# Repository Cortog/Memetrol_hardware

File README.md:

## Context
This repository contains the hardware design files for the Memetrol project. This project can control three washing machines and one dryer. Users can authenticate themselves using an RFID badge. The system logs the usage of the machines. A webserver on the system serves these logs to the administrator.

## Hardware
The hardware consists of a Raspberry Pi zero W and a Waveshare RP2040-zero both mounted on the base PCB. This PCB also contains the power supply, the relay drivers and analog circuitry for the current sensors. The Raspberry Pi is connected to the Waveshare RP2040-zero with UART. The Waveshare RP2040-zero is connected to the relay drivers and the current measurement circuitry. The Raspberry Pi is connected to the rest of the peripherals using a 20 pin ribbon cable. This cable goes to the door PCB, at which point the connections to the buttons, the LCD and the RFID reader are broken out.

## Changes for the next revision
- Not enough mounting holes were placed on the main PCB. In the end I drilled out the 2.5 mm mounting holes for the Raspberry Pi to 3 mm and drilled an extra one here: [image](extra_hole_location.png). In a future revision the mounting holes should be placed in the correct locations.
- R25 was not needed. This is the resistor in series with the buzzer. The volume can be controlled by varying the duty cycle of the PWM signal. This resistor should be removed in the next revision.
- The buzzer is not loud enough, a different buzzer should be used.
- The connectors for the relays should be changed, currently it consists of two connectors, one for + and one for ground. It should be changed to four connectors, one for each relay, this makes the connections more clear. The current labeling on the PCB is also not correct, where it says Ground it should be 12 volt.
- The analog circuitry for the current measurement could have its own 3.3 volt, or even a 1.65 volt regulator, this might make the measurements more stable.
- The rp2040-zero should know if the override switches are pressed, this would make calibration easier, since the rp2040-zero can then know if it should be measuring zero current or not.
- The electrolytic capacitors in the analog circuitry could be a lot smaller, these were only used because I had them laying around.
- An input power capacitory should be added.
- Maybe an aditional button should be added to the main PCB, this could be used for resetting passwords.
- In the current design a solderbridge is used to select between 5 volts and 12 volts for the button led power, with 12 volts being the default. However, the button leds can only handle up to 6 volts. The door PCB should be changed so that the leds can only be powered from the 5 volt rail.
- During the building of the PCB several mosfets broke, the gate was at around one volt even though it was being pulled down. After replacing them it was improved, but I also added a 10k resistor in parallel with the button leds which improved the leds realy turning off when the gate was being pulled down. This situation should be investigated further.
- Maybe an RFID interupt pin can be added to the door PCB, this would make the system more responsive and use less cpu time.
- The RFID and the LCD are on the same LCD bus, but this makes the RFID reader misbehave. Therefore it needs to be reset every time it is used. This should be fixed in the next revision.

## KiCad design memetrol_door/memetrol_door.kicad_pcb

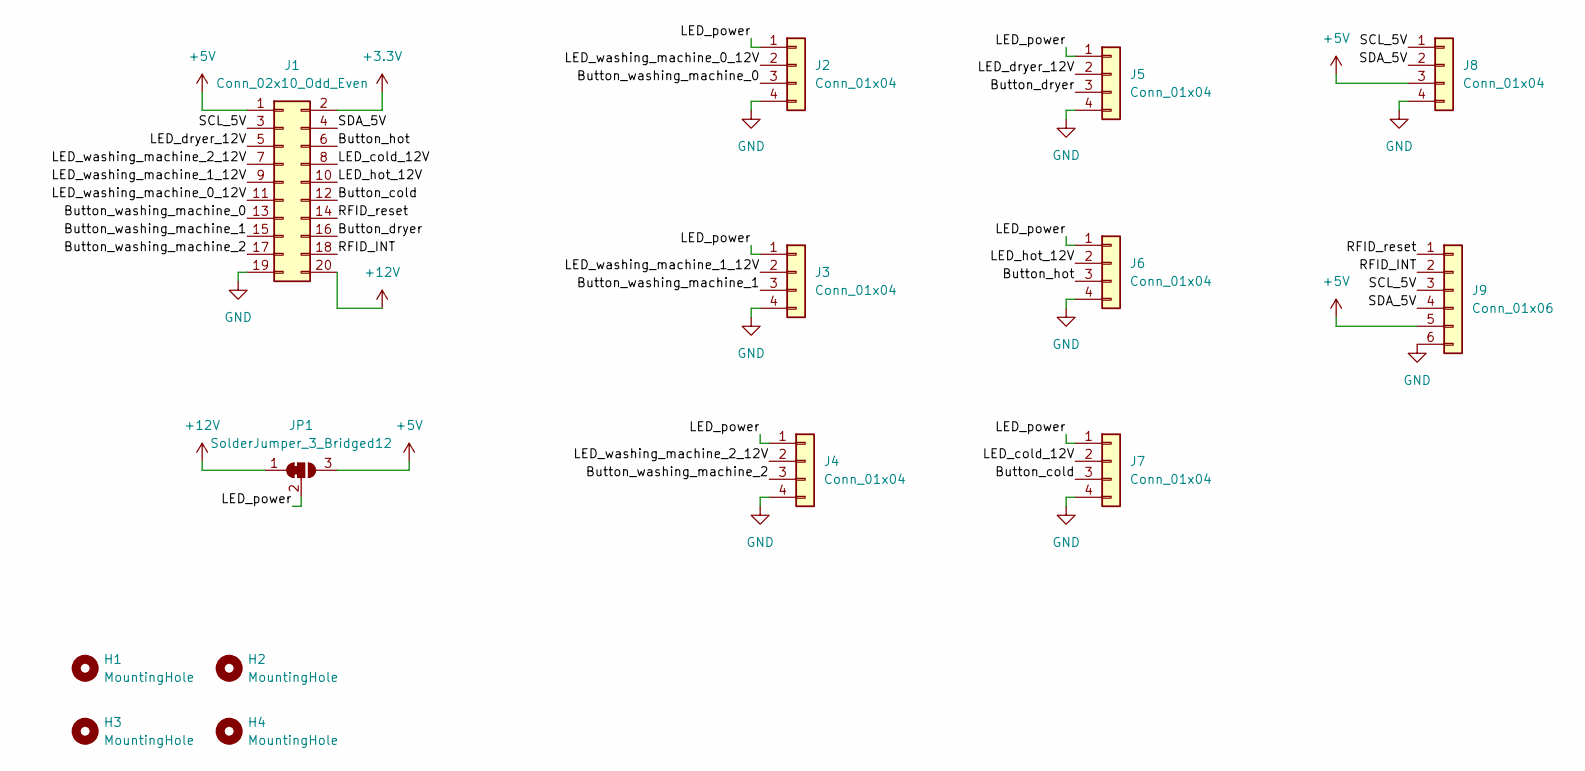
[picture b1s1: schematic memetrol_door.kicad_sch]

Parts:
H1, H2, H3, H4: MountingHole; MountingHole_3.2mm_M3
J1: Conn_02x10_Odd_Even; IDC-Header_2x10_P2.54mm_Vertical
J2, J3, J4, J5, J6, J7, J8: Conn_01x04; JST_PH_B4B-PH-K_1x04_P2.00mm_Vertical
J9: Conn_01x06; JST_PH_B6B-PH-K_1x06_P2.00mm_Vertical
JP1: SolderJumper_3_Bridged12; SolderJumper-3_P1.3mm_Bridged12_Pad1.0x1.5mm

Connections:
+3.3V: J1.2
+5V: J1.1, J8.3, J9.5, JP1.3 (B)
+12V: J1.20, JP1.1 (A)
/Button_cold: J1.12, J7.3
/Button_dryer: J1.16, J5.3
/Button_hot: J1.6, J6.3
/Button_washing_machine_0: J1.13, J2.3
/Button_washing_machine_1: J1.15, J3.3
/Button_washing_machine_2: J1.17, J4.3
/LED_cold_12V: J1.8, J7.2
/LED_dryer_12V: J1.5, J5.2
/LED_hot_12V: J1.10, J6.2
/LED_power: J2.1, J3.1, J4.1, J5.1, J6.1, J7.1, JP1.2 (C)
/LED_washing_machine_0_12V: J1.11, J2.2
/LED_washing_machine_1_12V: J1.9, J3.2
/LED_washing_machine_2_12V: J1.7, J4.2
/RFID_INT: J1.18, J9.2
/RFID_reset: J1.14, J9.1
/SCL_5V: J1.3, J8.1, J9.3
/SDA_5V: J1.4, J8.2, J9.4
GND: J1.19, J2.4, J3.4, J4.4, J5.4, J6.4, J7.4, J8.4, J9.6

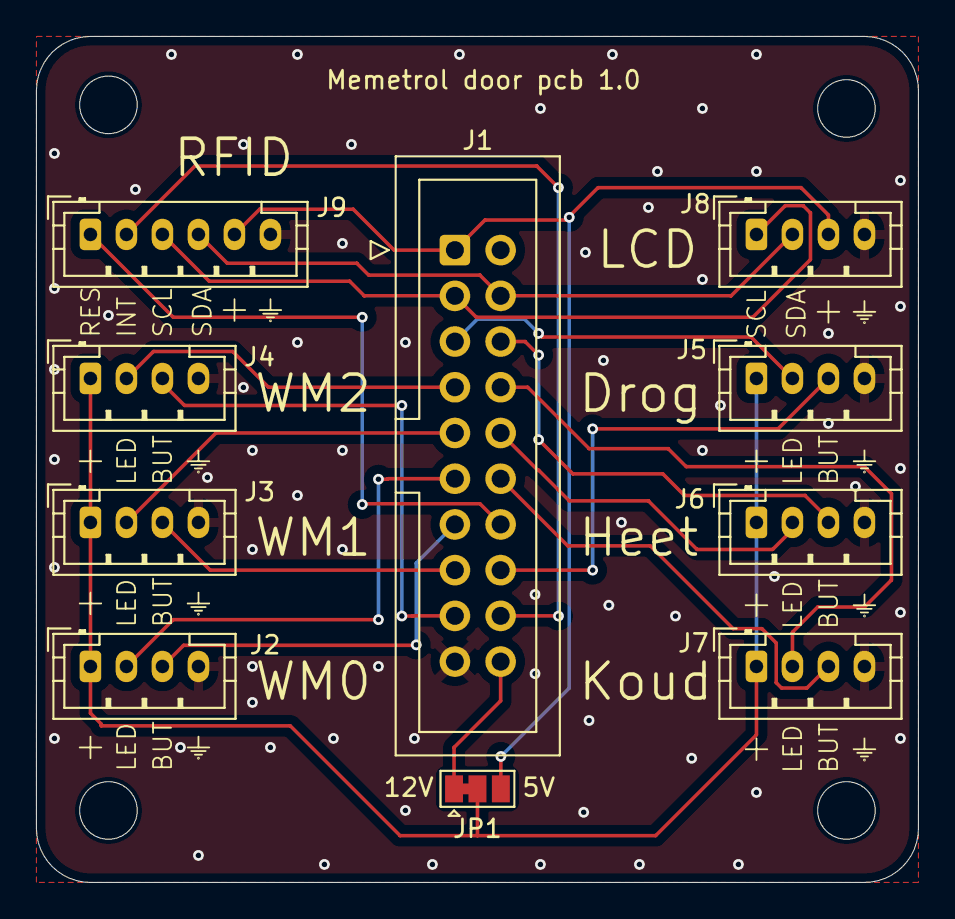
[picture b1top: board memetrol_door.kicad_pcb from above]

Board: 2 copper layers, 49.0 x 47.0 mm, 14 parts (0 on the bottom side), 20 nets.

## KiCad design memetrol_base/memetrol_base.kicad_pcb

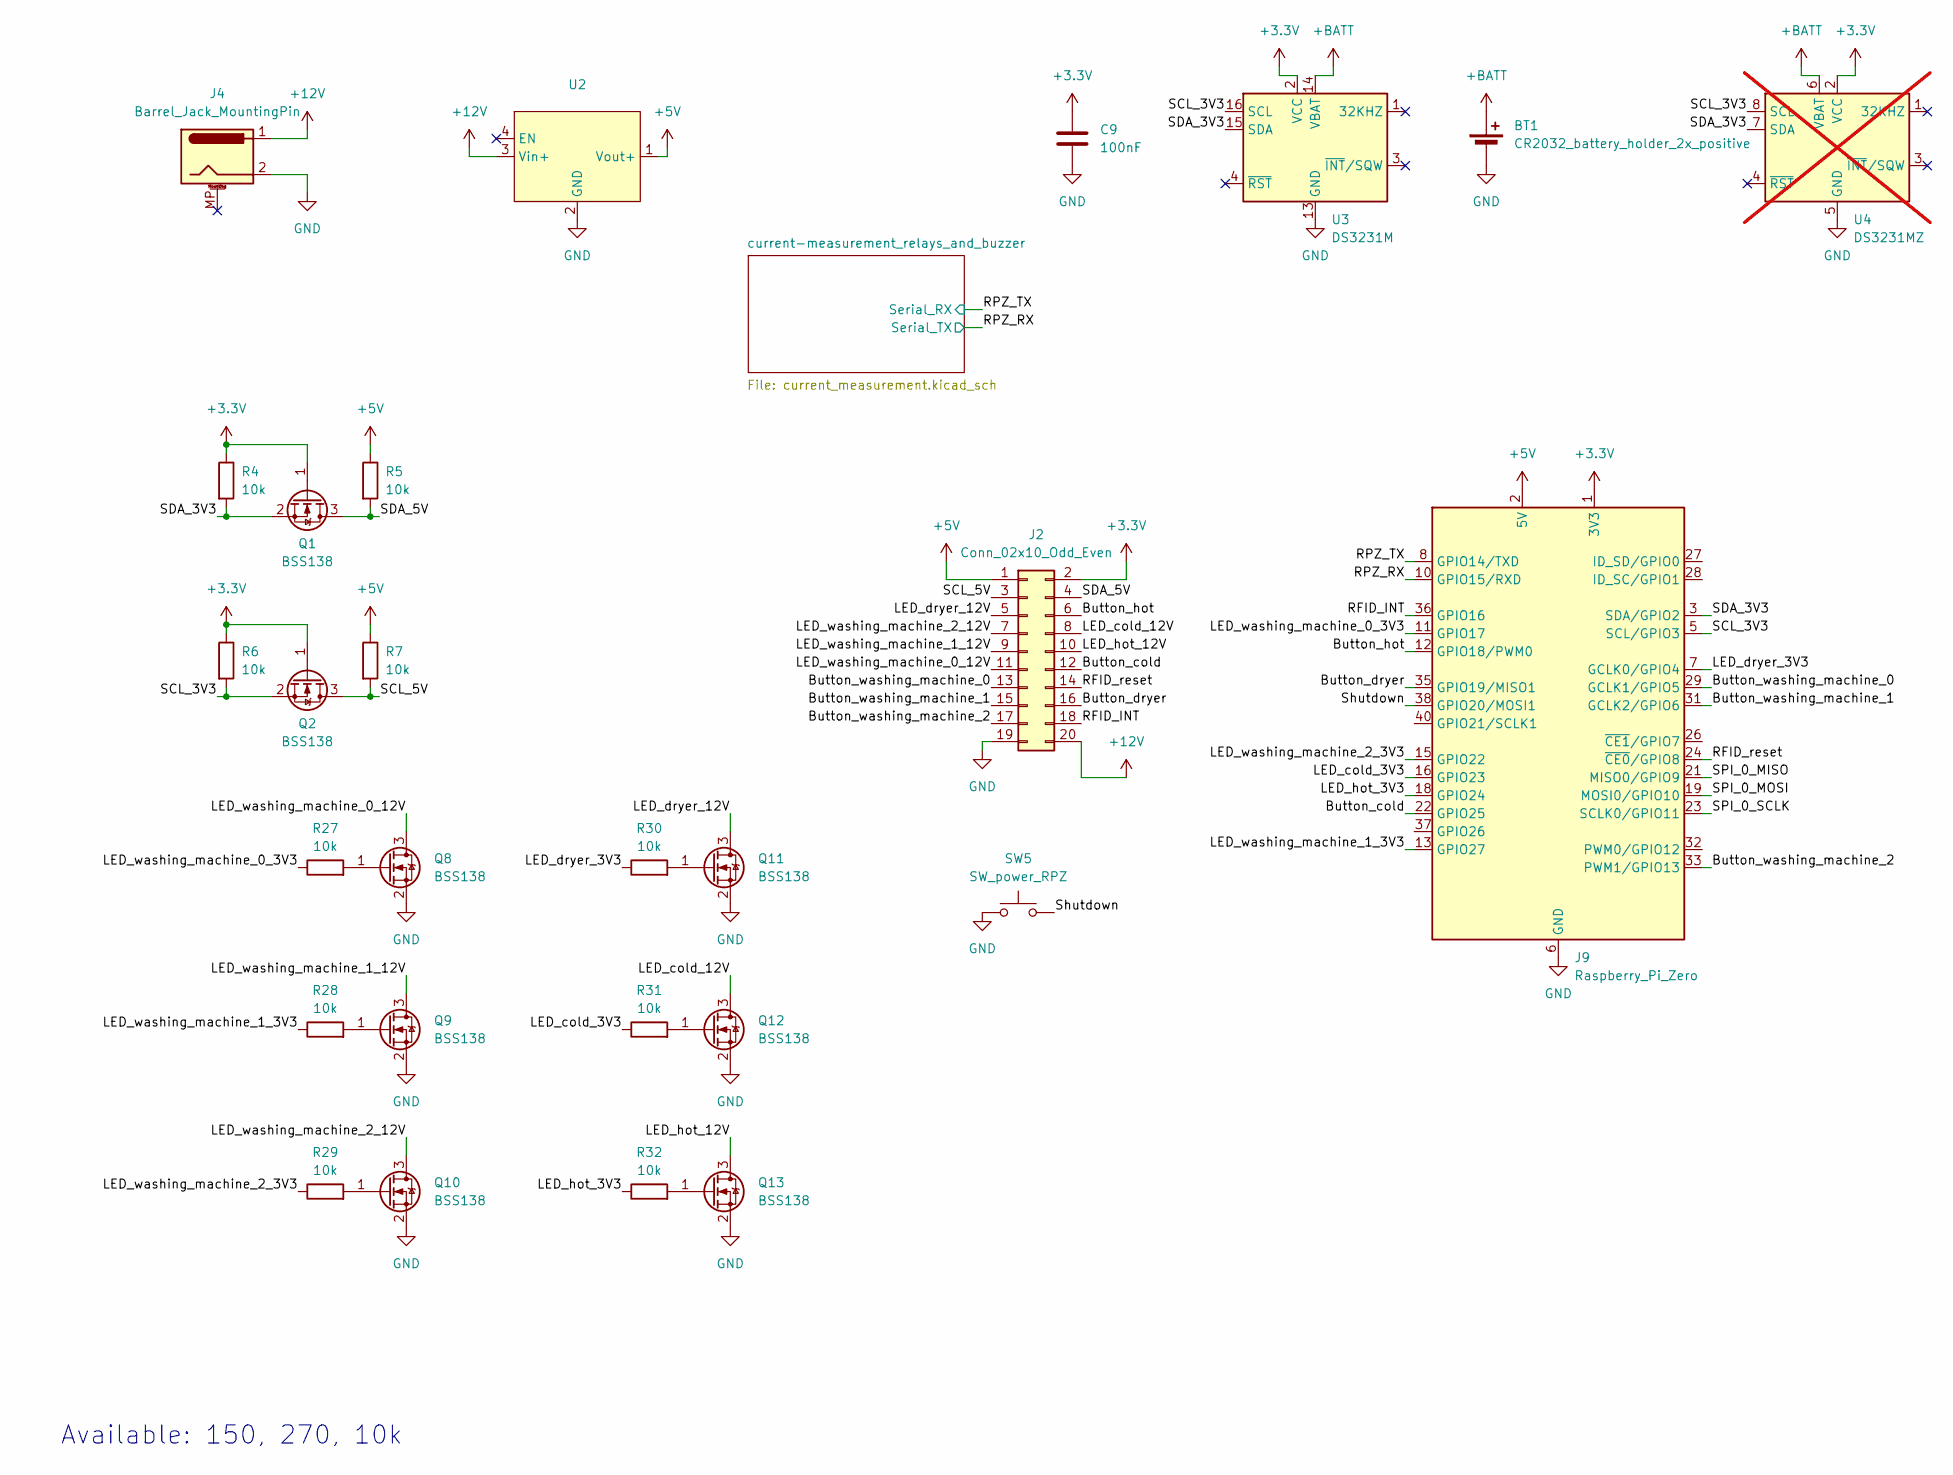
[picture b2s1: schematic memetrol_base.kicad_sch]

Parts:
BT1: CR2032_battery_holder_2x_positive; RS_PRO_CR2032_237-8358
C9: 100nF; C_0805_2012Metric_Pad1.18x1.45mm_HandSolder
J2: Conn_02x10_Odd_Even; IDC-Header_2x10_P2.54mm_Vertical
J4: Barrel_Jack_MountingPin; BarrelJack_Horizontal
J9: Raspberry_Pi_Zero; Raspberry_Pi_Zero_Socketed_THT_FaceUp_MountingHoles
Q1, Q2, Q8, Q9, Q10, Q11, Q12, Q13: BSS138; SOT-323_SC-70_Handsoldering
R4, R5, R6, R7, R27, R28, R29, R30, R31, R32: 10k; R_0805_2012Metric_Pad1.20x1.40mm_HandSolder
SW5: SW_power_RPZ; SW_PUSH_6mm_H7.3mm
U2: MP2315_board_vertical
U3: DS3231M; SOIC-16W_7.5x10.3mm_P1.27mm
U4: DS3231MZ; SOIC-8_3.9x4.9mm_P1.27mm; not fitted

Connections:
+3.3V: C9.1, J2.2, J9.1 (3V3), J9.17 (3V3), Q1.1 (G), Q2.1 (G), R4.1, R6.1, U3.2 (VCC), U4.2 (VCC)
+5V: J2.1, J9.2 (5V), J9.4 (5V), R5.1, R7.1, U2.1 (Vout+); also elsewhere on the board
+12V: J2.20, J4.1, U2.3 (Vin+); also elsewhere on the board
+BATT: BT1.1 (+), BT1.2 (+), U3.14 (VBAT), U4.6 (VBAT)
/Button_cold: J2.12, J9.22 (GPIO25)
/Button_dryer: J2.16, J9.35 (GPIO19/MISO1)
/Button_hot: J2.6, J9.12 (GPIO18/PWM0)
/Button_washing_machine_0: J2.13, J9.29 (GCLK1/GPIO5)
/Button_washing_machine_1: J2.15, J9.31 (GCLK2/GPIO6)
/Button_washing_machine_2: J2.17, J9.33 (PWM1/GPIO13)
/LED_cold_3V3: J9.16 (GPIO23), R31.1
/LED_cold_12V: J2.8, Q12.3 (D)
/LED_dryer_3V3: J9.7 (GCLK0/GPIO4), R30.1
/LED_dryer_12V: J2.5, Q11.3 (D)
/LED_hot_3V3: J9.18 (GPIO24), R32.1
/LED_hot_12V: J2.10, Q13.3 (D)
/LED_washing_machine_0_3V3: J9.11 (GPIO17), R27.1
/LED_washing_machine_0_12V: J2.11, Q8.3 (D)
/LED_washing_machine_1_3V3: J9.13 (GPIO27), R28.1
/LED_washing_machine_1_12V: J2.9, Q9.3 (D)
/LED_washing_machine_2_3V3: J9.15 (GPIO22), R29.1
/LED_washing_machine_2_12V: J2.7, Q10.3 (D)
/RFID_INT: J2.18, J9.36 (GPIO16)
/RFID_reset: J2.14, J9.24 (~CE0/GPIO8)
/RPZ_RX: J9.10 (GPIO15/RXD); also elsewhere on the board
/RPZ_TX: J9.8 (GPIO14/TXD); also elsewhere on the board
/SCL_3V3: J9.5 (SCL/GPIO3), Q2.2 (S), R6.2, U3.16 (SCL), U4.8 (SCL)
/SCL_5V: J2.3, Q2.3 (D), R7.2
/SDA_3V3: J9.3 (SDA/GPIO2), Q1.2 (S), R4.2, U3.15 (SDA), U4.7 (SDA)
/SDA_5V: J2.4, Q1.3 (D), R5.2
/SPI_0_MISO: J9.21 (MISO0/GPIO9)
/SPI_0_MOSI: J9.19 (MOSI0/GPIO10)
/SPI_0_SCLK: J9.23 (SCLK0/GPIO11)
/Shutdown: J9.38 (GPIO20/MOSI1), SW5.2
GND: BT1.3 (-), C9.2, J2.19, J4.2, J9.6 (GND), J9.9 (GND), J9.14 (GND), J9.20 (GND), J9.25 (GND), J9.30 (GND), J9.34 (GND), J9.39 (GND), Q8.2 (S), Q9.2 (S), Q10.2 (S), Q11.2 (S), Q12.2 (S), Q13.2 (S), SW5.1, U2.2 (GND), U3.5 (GND), U3.6 (GND), U3.7 (GND), U3.8 (GND), U3.9 (GND), U3.10 (GND), U3.11 (GND), U3.12 (GND), U3.13 (GND), U4.5 (GND); also elsewhere on the board
unnamed: Q8.1 (G), R27.2
unnamed: Q9.1 (G), R28.2
unnamed: Q10.1 (G), R29.2
unnamed: Q11.1 (G), R30.2
unnamed: Q12.1 (G), R31.2
unnamed: Q13.1 (G), R32.2

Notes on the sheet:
Available: 150, 270, 10k

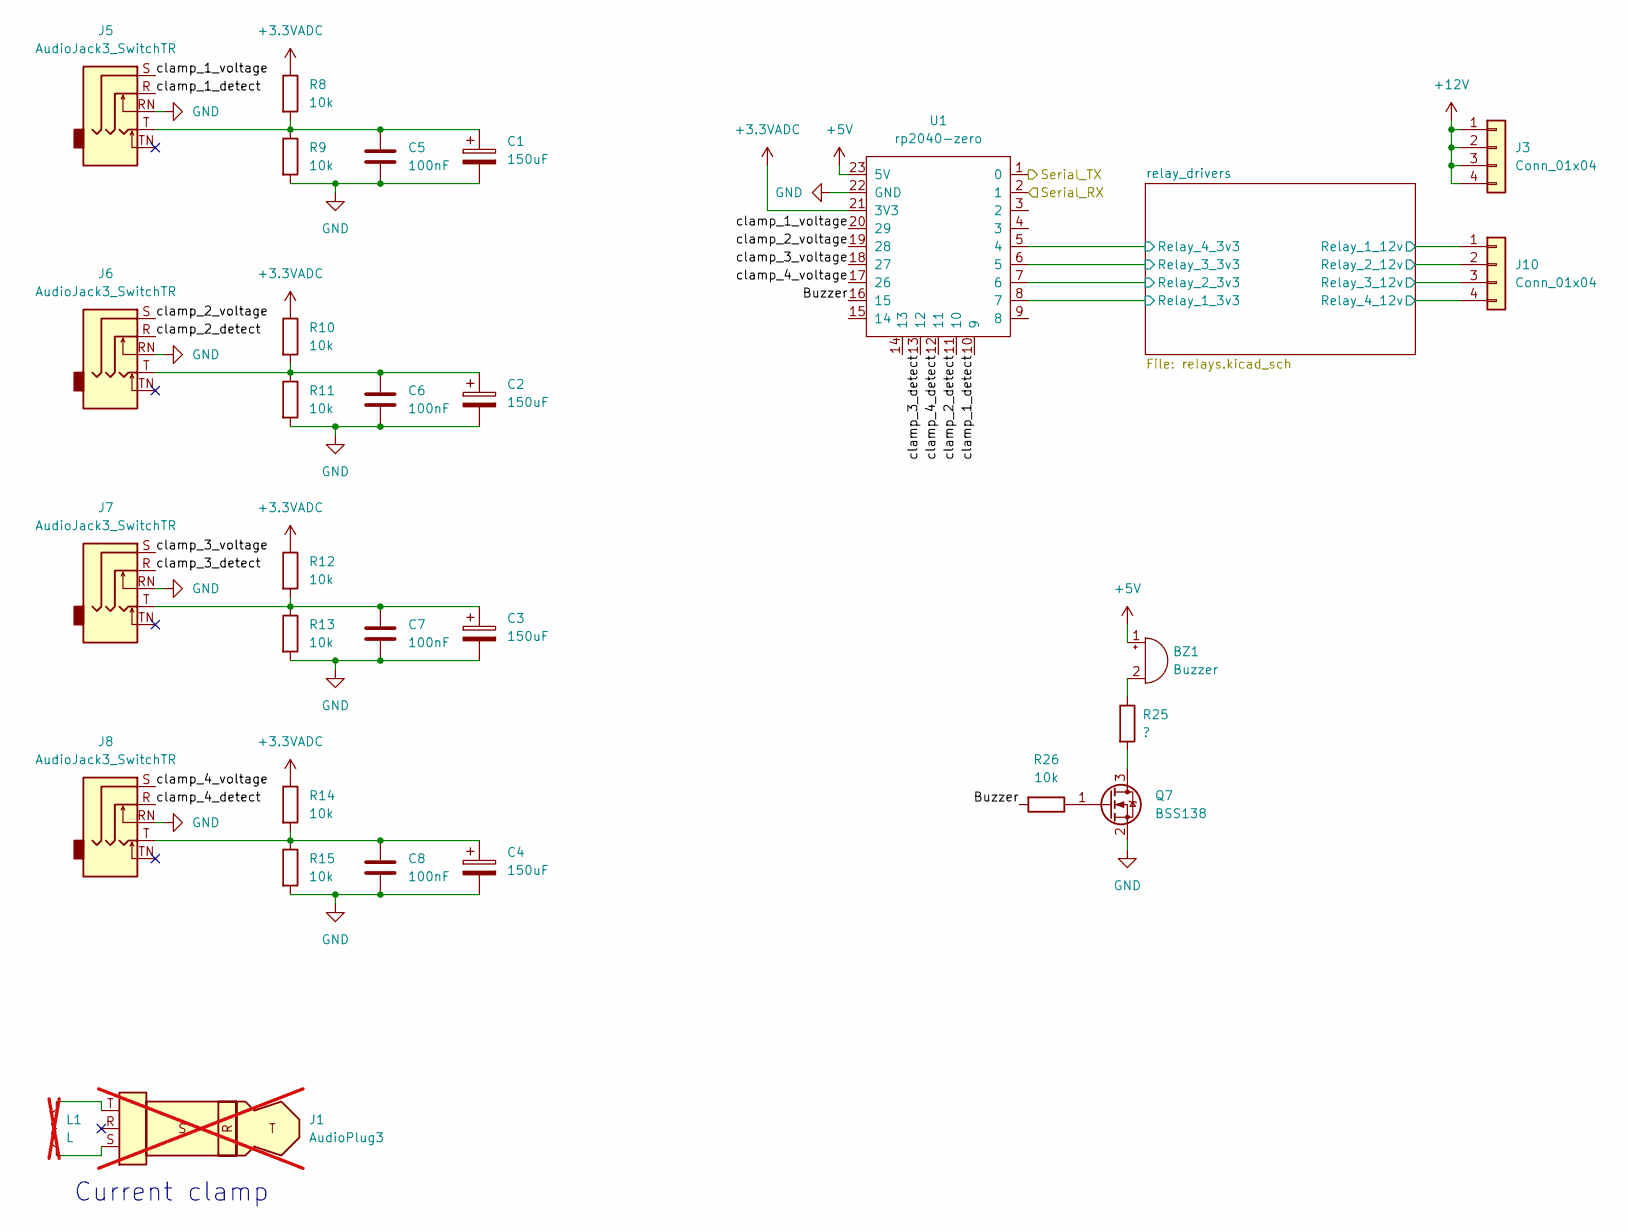
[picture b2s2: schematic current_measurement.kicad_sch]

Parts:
BZ1: Buzzer; MagneticBuzzer_ProSignal_ABT-410-RC
C1, C2, C3, C4: 150uF; CP_Elec_5x5.3
C5, C6, C7, C8: 100nF; C_0805_2012Metric_Pad1.18x1.45mm_HandSolder
J1: AudioPlug3; not fitted
J3, J10: Conn_01x04; 8971039
J5, J6, J7, J8: AudioJack3_SwitchTR; Jack_3.5mm_CUI_SJ1-3525N_Horizontal
L1: L; not fitted
Q7: BSS138; SOT-323_SC-70_Handsoldering
R8, R9, R10, R11, R12, R13, R14, R15, R26: 10k; R_0805_2012Metric_Pad1.20x1.40mm_HandSolder
R25: ?; R_Axial_DIN0207_L6.3mm_D2.5mm_P10.16mm_Horizontal
U1: rp2040-zero; rp2040-zero-tht

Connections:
+3.3VADC: R8.1, R10.1, R12.1, R14.1, U1.21 (3V3); also elsewhere on the board
+5V: BZ1.1 (+), U1.23 (5V); also elsewhere on the board
+12V: J3.1, J3.2, J3.3, J3.4; also elsewhere on the board
/RPZ_RX: U1.1 (0); also elsewhere on the board
/RPZ_TX: U1.2 (1); also elsewhere on the board
/current-measurement_relays_and_buzzer/Buzzer: R26.2, U1.16 (15)
/current-measurement_relays_and_buzzer/clamp_1_detect: J5.R, U1.10 (9)
/current-measurement_relays_and_buzzer/clamp_1_voltage: J5.S, U1.20 (29)
/current-measurement_relays_and_buzzer/clamp_2_detect: J6.R, U1.11 (10)
/current-measurement_relays_and_buzzer/clamp_2_voltage: J6.S, U1.19 (28)
/current-measurement_relays_and_buzzer/clamp_3_detect: J7.R, U1.13 (12)
/current-measurement_relays_and_buzzer/clamp_3_voltage: J7.S, U1.18 (27)
/current-measurement_relays_and_buzzer/clamp_4_detect: J8.R, U1.12 (11)
/current-measurement_relays_and_buzzer/clamp_4_voltage: J8.S, U1.17 (26)
/current-measurement_relays_and_buzzer/relay_drivers/Relay_1_3v3: U1.8 (7); also elsewhere on the board
/current-measurement_relays_and_buzzer/relay_drivers/Relay_1_12v: J10.1; also elsewhere on the board
/current-measurement_relays_and_buzzer/relay_drivers/Relay_2_3v3: U1.7 (6); also elsewhere on the board
/current-measurement_relays_and_buzzer/relay_drivers/Relay_2_12v: J10.2; also elsewhere on the board
/current-measurement_relays_and_buzzer/relay_drivers/Relay_3_3v3: U1.6 (5); also elsewhere on the board
/current-measurement_relays_and_buzzer/relay_drivers/Relay_3_12v: J10.3; also elsewhere on the board
/current-measurement_relays_and_buzzer/relay_drivers/Relay_4_3v3: U1.5 (4); also elsewhere on the board
/current-measurement_relays_and_buzzer/relay_drivers/Relay_4_12v: J10.4; also elsewhere on the board
GND: C1.2, C2.2, C3.2, C4.2, C5.2, C6.2, C7.2, C8.2, J5.RN, J6.RN, J7.RN, J8.RN, Q7.2 (S), R9.2, R11.2, R13.2, R15.2, U1.22 (GND); also elsewhere on the board
unnamed: BZ1.2 (-), R25.1
unnamed: C1.1, C5.1, J5.T, R8.2, R9.1
unnamed: C2.1, C6.1, J6.T, R10.2, R11.1
unnamed: C3.1, C7.1, J7.T, R12.2, R13.1
unnamed: C4.1, C8.1, J8.T, R14.2, R15.1
unnamed: J1.S, L1.1
unnamed: J1.T, L1.2
unnamed: Q7.3 (D), R25.2
unnamed: Q7.1 (G), R26.1

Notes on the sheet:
Current clamp

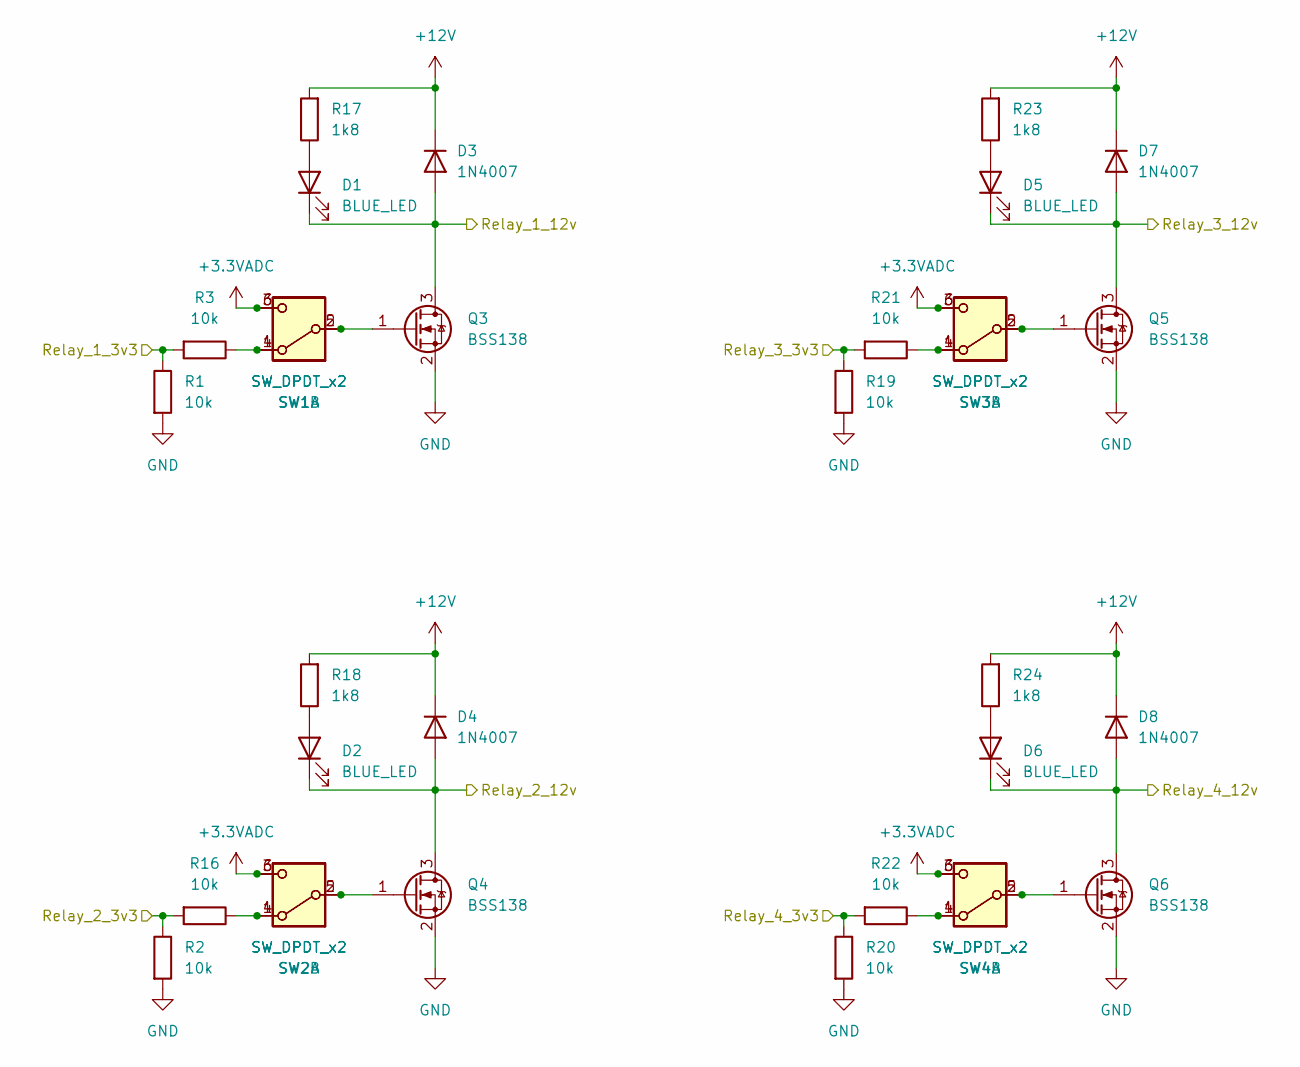
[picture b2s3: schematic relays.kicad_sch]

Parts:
D1, D2, D5, D6: BLUE_LED; LED_0805_2012Metric_Pad1.15x1.40mm_HandSolder
D3, D4, D7, D8: 1N4007; D_SOD-123F
Q3, Q4, Q5, Q6: BSS138; SOT-323_SC-70_large_drain
R1, R2, R3, R16, R19, R20, R21, R22: 10k; R_0805_2012Metric_Pad1.20x1.40mm_HandSolder
R17, R18, R23, R24: 1k8; R_0805_2012Metric_Pad1.20x1.40mm_HandSolder
SW1, SW2, SW3, SW4: SW_DPDT_x2; DPDT_7x7mm_blue-white

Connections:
+3.3VADC: SW1.3 (C), SW1.6 (C), SW2.3 (C), SW2.6 (C), SW3.3 (C), SW3.6 (C), SW4.3 (C), SW4.6 (C); also elsewhere on the board
+12V: D3.1 (K), D4.1 (K), D7.1 (K), D8.1 (K), R17.2, R18.2, R23.2, R24.2; also elsewhere on the board
/current-measurement_relays_and_buzzer/relay_drivers/Relay_1_3v3: R1.1, R3.2; also elsewhere on the board
/current-measurement_relays_and_buzzer/relay_drivers/Relay_1_12v: D1.1 (K), D3.2 (A), Q3.3 (D); also elsewhere on the board
/current-measurement_relays_and_buzzer/relay_drivers/Relay_2_3v3: R2.1, R16.2; also elsewhere on the board
/current-measurement_relays_and_buzzer/relay_drivers/Relay_2_12v: D2.1 (K), D4.2 (A), Q4.3 (D); also elsewhere on the board
/current-measurement_relays_and_buzzer/relay_drivers/Relay_3_3v3: R19.1, R21.2; also elsewhere on the board
/current-measurement_relays_and_buzzer/relay_drivers/Relay_3_12v: D5.1 (K), D7.2 (A), Q5.3 (D); also elsewhere on the board
/current-measurement_relays_and_buzzer/relay_drivers/Relay_4_3v3: R20.1, R22.2; also elsewhere on the board
/current-measurement_relays_and_buzzer/relay_drivers/Relay_4_12v: D6.1 (K), D8.2 (A), Q6.3 (D); also elsewhere on the board
GND: Q3.2 (S), Q4.2 (S), Q5.2 (S), Q6.2 (S), R1.2, R2.2, R19.2, R20.2; also elsewhere on the board
unnamed: D1.2 (A), R17.1
unnamed: D2.2 (A), R18.1
unnamed: D5.2 (A), R23.1
unnamed: D6.2 (A), R24.1
unnamed: Q3.1 (G), SW1.2 (B), SW1.5 (B)
unnamed: Q4.1 (G), SW2.2 (B), SW2.5 (B)
unnamed: Q5.1 (G), SW3.2 (B), SW3.5 (B)
unnamed: Q6.1 (G), SW4.2 (B), SW4.5 (B)
unnamed: R3.1, SW1.1 (A), SW1.4 (A)
unnamed: R16.1, SW2.1 (A), SW2.4 (A)
unnamed: R21.1, SW3.1 (A), SW3.4 (A)
unnamed: R22.1, SW4.1 (A), SW4.4 (A)

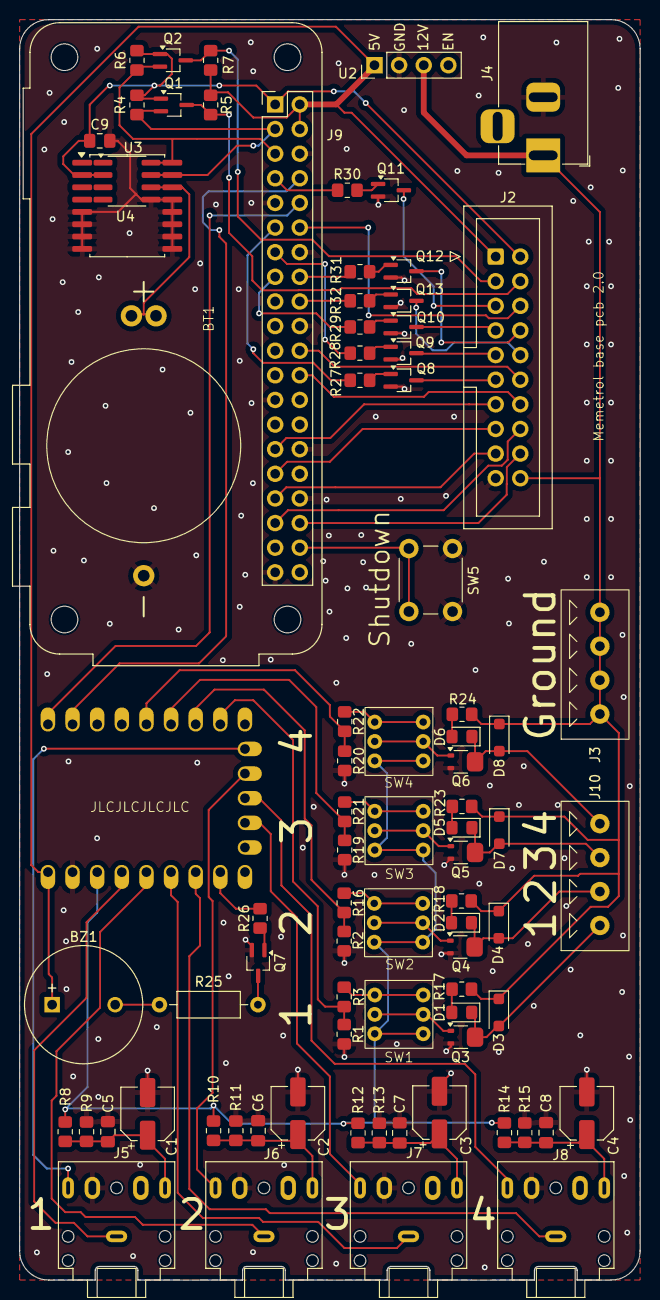
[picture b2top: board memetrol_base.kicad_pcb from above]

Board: 2 copper layers, 63.9 x 130.0 mm, 82 parts (0 on the bottom side), 75 nets.

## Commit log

2024-10-11 Initial push
2024-10-11 README change
2024-10-11 added another change for next revision
2024-10-11 Added yet another change for the next revision
